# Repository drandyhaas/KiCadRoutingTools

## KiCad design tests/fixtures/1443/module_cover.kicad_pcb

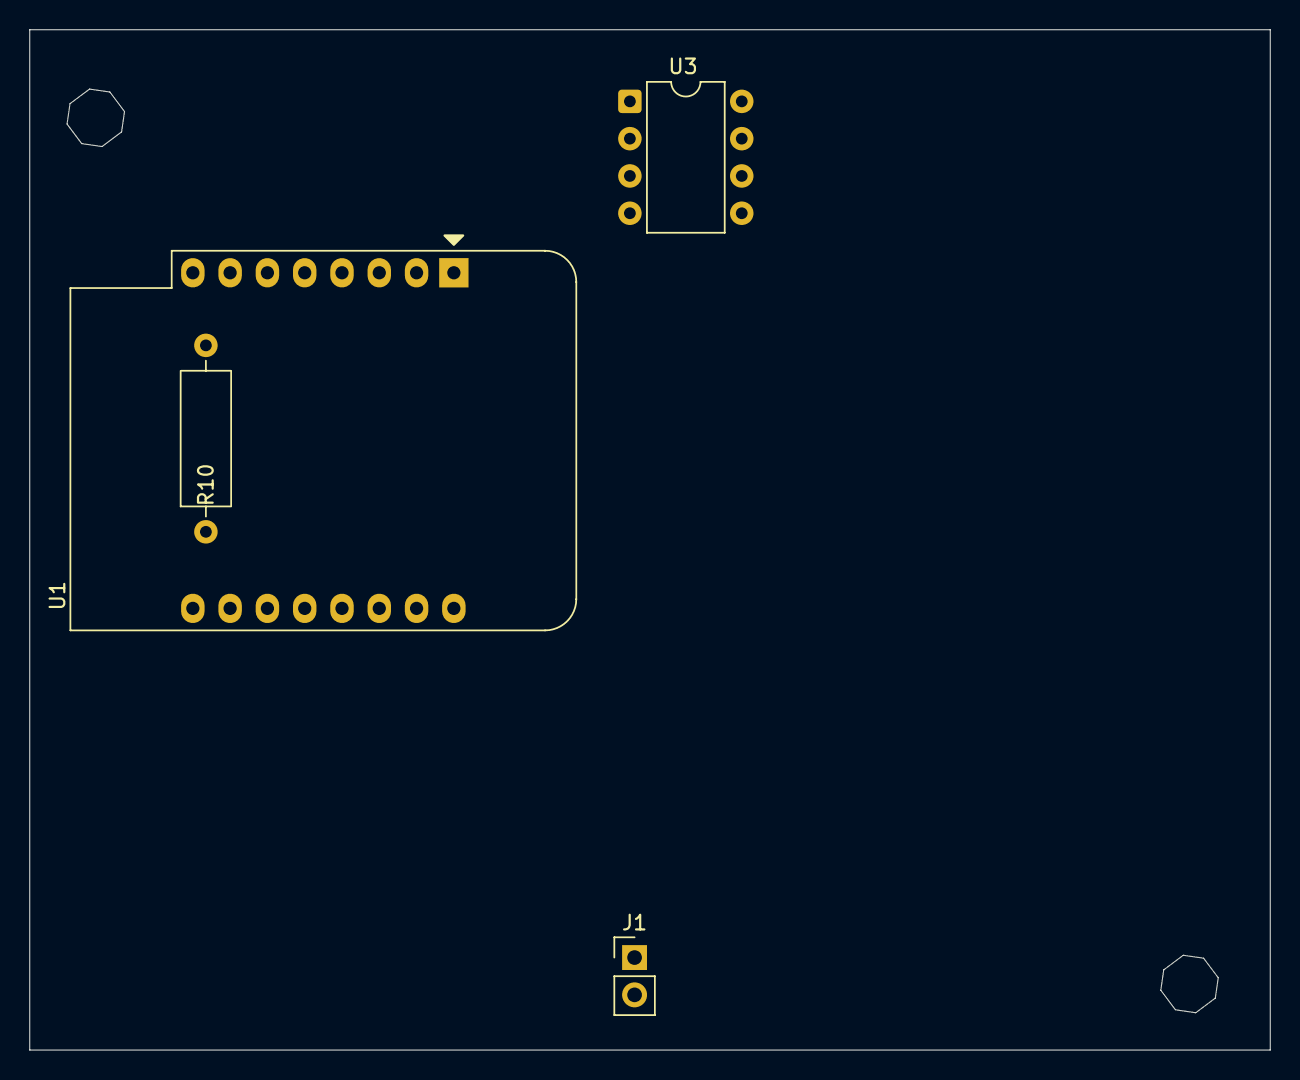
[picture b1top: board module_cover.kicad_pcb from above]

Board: 2 copper layers, 84.5 x 69.5 mm, 4 parts (0 on the bottom side), 3 nets, no tracks yet.

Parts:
J1: MP1584EN OUT +5V; PinHeader_1x02_P2.54mm_Vertical
R10: 10k; R_Axial_DIN0309_L9.0mm_D3.2mm_P12.70mm_Horizontal
U1: WEMOS_D1_mini; WEMOS_D1_mini_light
U3: LM358; DIP-8_W7.62mm

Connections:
unnamed: J1.1, J1.2
unnamed: R10.1, U1.10 (GND)
unnamed: R10.2, U1.7 (CS/D8)

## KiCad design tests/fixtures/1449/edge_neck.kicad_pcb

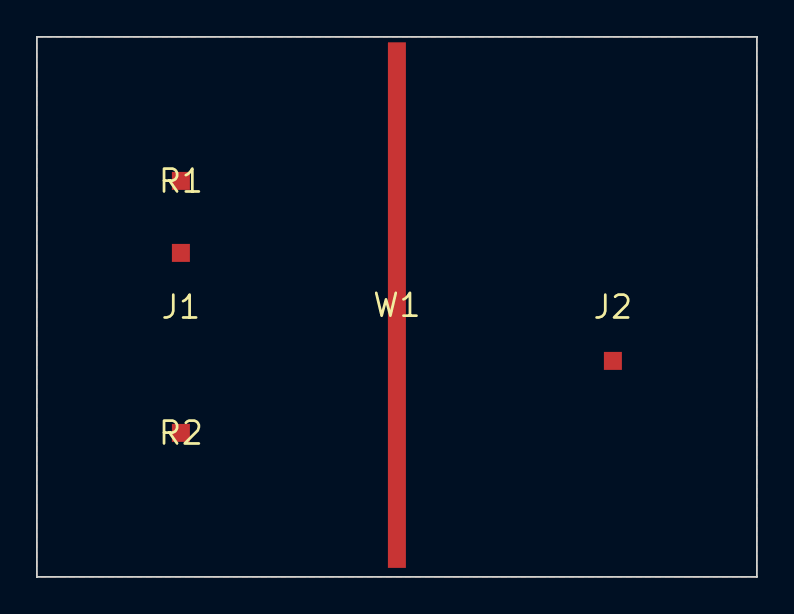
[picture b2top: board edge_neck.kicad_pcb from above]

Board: 2 copper layers, 40.0 x 30.0 mm, 5 parts (0 on the bottom side), 2 nets, no tracks yet.

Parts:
J1, J2: (no value)
R1, R2: (no value)
W1: (no value)

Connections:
GND: J1.1, J2.1
SIG: R1.1, R2.1

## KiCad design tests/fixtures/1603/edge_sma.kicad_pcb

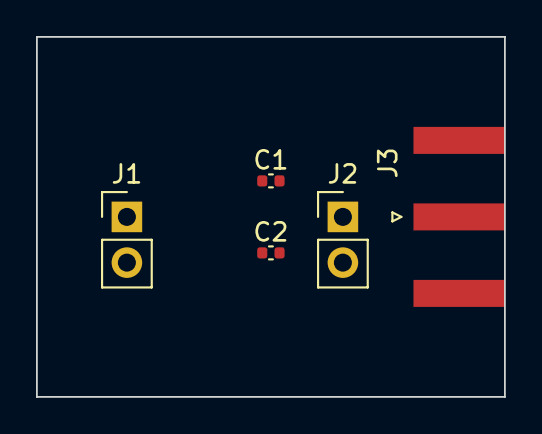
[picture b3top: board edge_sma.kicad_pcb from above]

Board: 2 copper layers, 26.0 x 20.0 mm, 5 parts (0 on the bottom side), 4 nets, no tracks yet.

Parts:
C1, C2: C_0402_1005Metric
J1, J2: PinHeader_1x02_P2.54mm_Vertical
J3: SMA_Amphenol_132289_EdgeMount

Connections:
DPA_N: C2.1, J1.2
DPA_P: C1.1, J1.1, J3.1
DPB_N: C2.2, J2.2
DPB_P: C1.2, J2.1
